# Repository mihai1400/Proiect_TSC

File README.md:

# Arhitectura Sistemului

## 1. Arhitectura Generală
Sistemul este construit în jurul **ESP32-C6-WROOM-1-N8** (microcontroler Wi-Fi 6 + Bluetooth 5 cu RISC-V) și include:

- **Alimentare & Baterie** (LDO, încărcător Li-Po, monitorizare nivel baterie)
- **Memorie** (Flash extern NOR 64MB, slot SD)
- **Senzori** (BME688 - temperatură/umiditate/presiune/VOC)
- **Afișaj** (E-Paper SPI)
- **Periferice** (RTC DS3231, butoane, LED-uri, USB-C)

## 2. Module & Interfețe cu ESP32-C6

### 2.1. Alimentare & Baterie
| Componentă                     | Interfață cu ESP32-C6       | Detalii                                  |
|--------------------------------|-----------------------------|------------------------------------------|
| LDO (XC6220A331MR-G)           | Nu (alimentare 3.3V)        | Reglează 3.3V pentru întreg sistemul     |
| Încărcător Baterie (MCP73831)  | GPIO4 (STAT)                | Semnalizează starea încărcării (LED)     |
| Monitor Baterie (MAX17048)     | I2C (SDA: GPIO8, SCL: GPIO9)| Măsoară nivelul bateriei (%/tensiune)    |

**Calcul consum:**
- ESP32-C6 (~80 mA în mod activ, ~5 µA în sleep)
- BME688 (~2.5 mA când active)
- E-Paper (~100 mA la refresh)
- **Total estimat:** ~200 mA (utilizare normală), sub 1 mA în sleep cu RTC activ

### 2.2. Memorie & Stocare
| Componentă            | Interfață cu ESP32-C6                          | Detalii                          |
|-----------------------|-----------------------------------------------|----------------------------------|
| Flash NOR (W25Q512JVEIQ) | SPI0 (CS: GPIO12, CLK: GPIO14, MOSI: GPIO13, MISO: GPIO11) | Stochează firmware/date |
| Slot SD (J4)          | SPI1 (CS: GPIO5, CLK: GPIO6, MOSI: GPIO7, MISO: GPIO10) | Stocare fișiere (FAT32) |

### 2.3. Senzori
| Componentă   | Interfață cu ESP32-C6       | Detalii                                  |
|--------------|-----------------------------|------------------------------------------|
| BME688       | I2C (SDA: GPIO8, SCL: GPIO9)| Senzor ambiental (temperatură, umiditate, presiune, VOC) |
| RTC (DS3231SN) | I2C (SDA: GPIO8, SCL: GPIO9)| Ceas precis (±2 ppm) cu alarmă           |

**Comunicație:**
- BME688 folosește I2C la 400 kHz (adresă `0x76`)
- DS3231 folosește I2C la 100 kHz (adresă `0x68`)

### 2.4. Afișaj E-Paper
| Componentă      | Interfață cu ESP32-C6                          | Detalii                          |
|-----------------|-----------------------------------------------|----------------------------------|
| Driver E-Paper  | SPI2 (CS: GPIO15, DC: GPIO16, RST: GPIO17, BUSY: GPIO18) | SPI dedicat pentru afișaj |

**Specificații:**
- Rezoluție: 800x600 (4.2" monocrom)
- Consum: ~100 mA la refresh, 0 mA în stare statică

### 2.5. Periferice & I/O
| Componentă   | Interfață cu ESP32-C6       | Detalii                                  |
|--------------|-----------------------------|------------------------------------------|
| Buton BOOT   | GPIO0                       | Resetare în mod flash                   |
| Buton CHANGE | GPIO1                       | Schimbă afișajul                        |
| LED-uri (D1-D12) | GPIO2, GPIO3            | Indicatori vizuali                      |
| USB-C (J1)   | GPIO20 (D+), GPIO21 (D-)    | Comunicație serială (CDC)               |

## 3. Alocarea Pinilor ESP32-C6
| Pin ESP32-C6 | Funcție       | Componentă            |
|--------------|---------------|-----------------------|
| GPIO0        | BOOT          | Buton BOOT            |
| GPIO1        | INPUT         | Buton CHANGE          |
| GPIO2-3      | OUTPUT        | LED-uri               |
| GPIO4        | INPUT         | MCP73831 (STAT)       |
| GPIO5        | CS            | Slot SD               |
| GPIO6-7      | SCK/MOSI      | Slot SD               |
| GPIO8-9      | SDA/SCL       | BME688 + DS3231 (I2C) |
| GPIO10       | MISO          | Slot SD               |
| GPIO11       | MISO          | Flash NOR             |
| GPIO12       | CS            | Flash NOR             |
| GPIO13-14    | MOSI/SCK      | Flash NOR             |
| GPIO15-18    | SPI EPD       | Afișaj E-Paper        |
| GPIO20-21    | USB D+/D-     | USB-C                 |

## 4. Optimizare Consum Energie
- **Sleep Mode:** ESP32-C6 intră în Deep Sleep cu RTC activ (~5 µA), trezit de DS3231 (alarmă) sau butoane
- **E-Paper:** Folosește energie doar la refresh
- **Senzori:** BME688 este pornit periodic (e.g., la 1 minut)

## 5. Diagramă

## 6. BOM

| Device Module                       | Amount | Datasheet | Shop |
| ----------------------------------- | ------ | -------| --------|
| 112A-TAAR-R03_ATTEND                | 1      | https://www.attend.com.tw/en/product.php?act=view&id=253 | https://www.digikey.com/en/products/detail/attend-technology/112A-TAAR-R03/17633923 |
| BD5229G-TR                          | 1      | https://www.digikey.ph/en/products/detail/rohm-semiconductor/BD5229G-TR/658502 | https://www.digikey.ph/en/products/detail/rohm-semiconductor/BD5229G-TR/658502 |
| BUTTON_COSYOMV1                     | 3      | https://components101.com/switches/push-button | https://uk.farnell.com/wurth-elektronik/430182043816/switch-160gf-6x6mm-smd-4-3mm-act/dp/2065105?CMP=GRHB-OEMSECRETS101 |
| CPH3225A                            | 1      | https://www.digikey.com/en/products/detail/seiko-instruments/CPH3225A/8692444 | https://www.digikey.com/en/products/detail/seiko-instruments/CPH3225A/8692444 |
| DS3231SN                            | 1      | https://www.digikey.com/en/products/detail/analog-devices-inc-maxim-integrated/DS3231SN/1197576 | https://www.digikey.com/en/products/detail/analog-devices-inc-maxim-integrated/DS3231SN/1197576 |
| BME680                              | 1      | https://www.sparkfun.com/sparkfun-environmental-sensor-breakout-bme680-qwiic.html | https://www.sparkfun.com/sparkfun-environmental-sensor-breakout-bme680-qwiic.html |
| MCP73831                            | 1      | https://www.microchip.com/en-us/product/mcp73831 | https://www.microchipdirect.com/product/MCP73831T-2ADI/OT |
| C6-WROOM-1-N8                       | 1      | https://www.espressif.com/sites/default/files/documentation/esp32-c6-wroom-1_wroom-1u_datasheet_en.pdf | https://www.adafruit.com/product/5671 |
| FH34SRJ-24S-0.5SH_99_               | 1      | https://www.hirose.com/product/p/CL0580-1255-6-99 | https://www.hirose.com/product/p/CL0580-1255-6-99 |
| MAX17048G+T10                       | 1      | https://eu.mouser.com/ProductDetail/Analog-Devices-Maxim-Integrated/MAX17048G+T10?qs=D7PJwyCwLAoGnnn8jEPRBQ%3D%3D | https://eu.mouser.com/ProductDetail/Analog-Devices-Maxim-Integrated/MAX17048G+T10?qs=D7PJwyCwLAoGnnn8jEPRBQ%3D%3D |
| MBR0530                             | 3      | https://www.digikey.com/en/products/detail/onsemi/MBR0530/1048783 | https://www.digikey.com/en/products/detail/onsemi/MBR0530/1048783 |
| PGB1010603MR                        | 6      | https://www.digikey.com/en/products/detail/littelfuse-inc/PGB1010603MR/715755 | https://www.digikey.com/en/products/detail/littelfuse-inc/PGB1010603MR/715755 |
| SAMACSYS_PARTS_USB4110-GF-A         | 1      | https://www.digikey.ro/en/products/detail/gct/USB4110-GF-A/10384547 | https://www.digikey.ro/en/products/detail/gct/USB4110-GF-A/10384547 |
| SI1308EDL-T1-GE3                    | 1      | https://www.digikey.com/en/products/detail/vishay-siliconix/SI1308EDL-T1-GE3/4876435 | https://www.digikey.com/en/products/detail/vishay-siliconix/SI1308EDL-T1-GE3/4876435 |
| SJ                                  | 1      | https://www.digikey.com/en/products/detail/cui-devices/SJ1-3514N/738685 | https://www.digikey.com/en/products/detail/cui-devices/SJ1-3514N/738685 |
| USBLC6-2SC6Y                        | 1      | https://www.digikey.com/en/products/detail/stmicroelectronics/USBLC6-2SC6Y/2819177 | https://www.digikey.com/en/products/detail/stmicroelectronics/USBLC6-2SC6Y/2819177 |
| W25Q512JVEIQ                        | 1      | https://www.digikey.com/en/products/detail/winbond-electronics/W25Q512JVEIQ/10244706 | https://www.digikey.com/en/products/detail/winbond-electronics/W25Q512JVEIQ/10244706 |
| XC6220A331MR-G                      | 1      | https://www.digikey.com/en/products/detail/torex-semiconductor-ltd/XC6220B331MR-G/2138177 | https://www.digikey.com/en/products/detail/torex-semiconductor-ltd/XC6220B331MR-G/2138177 |
| SD0805S020S1R0                      | 2      | https://www.digikey.com/en/products/detail/kyocera-avx/SD0805S020S1R0/3749517 | https://www.digikey.com/en/products/detail/kyocera-avx/SD0805S020S1R0/3749517 |
| LTSPICE_C 100nF                     | 8      | https://www.digikey.com/en/products/detail/nextgen-components/0402B104K500HI/22601924 | https://www.digikey.com/en/products/detail/nextgen-components/0402B104K500HI/22601924 |
| LTSPICE_C 10nF                      | 1      | https://www.amazon.com/ALLECIN-Electrolytic-Capacitor-0-2x0-43in-Capacitors/dp/B0CMQC587X/ref=sr_1_1_sspa?sr=8-1-spons&sp_csd=d2lkZ2V0TmFtZT1zcF9hdGY&psc=1 | https://www.amazon.com/ALLECIN-Electrolytic-Capacitor-0-2x0-43in-Capacitors/dp/B0CMQC587X/ref=sr_1_1_sspa?sr=8-1-spons&sp_csd=d2lkZ2V0TmFtZT1zcF9hdGY&psc=1 |
| LTSPICE_C 4.7uF                     | 6      | https://www.amazon.com/ALLECIN-Electrolytic-Capacitor-0-2x0-43in-Capacitors/dp/B0CMQC587X/ref=sr_1_1_sspa?sr=8-1-spons&sp_csd=d2lkZ2V0TmFtZT1zcF9hdGY&psc=1 | https://www.amazon.com/ALLECIN-Electrolytic-Capacitor-0-2x0-43in-Capacitors/dp/B0CMQC587X/ref=sr_1_1_sspa?sr=8-1-spons&sp_csd=d2lkZ2V0TmFtZT1zcF9hdGY&psc=1 |
| LTSPICE_C 1uF                       | 10     | https://www.amazon.com/ALLECIN-Electrolytic-Capacitor-0-2x0-43in-Capacitors/dp/B0CMQC587X/ref=sr_1_1_sspa?sr=8-1-spons&sp_csd=d2lkZ2V0TmFtZT1zcF9hdGY&psc=1 | https://www.amazon.com/ALLECIN-Electrolytic-Capacitor-0-2x0-43in-Capacitors/dp/B0CMQC587X/ref=sr_1_1_sspa?sr=8-1-spons&sp_csd=d2lkZ2V0TmFtZT1zcF9hdGY&psc=1 |
| LTSPICE_C 0.1uF                     | 1      | https://www.digikey.com/en/products/detail/samsung-electro-mechanics/CL10E104KC8VPNC/20498486 | https://www.digikey.com/en/products/detail/samsung-electro-mechanics/CL10E104KC8VPNC/20498486 |
| ADAFRUIT_LED                        | 1      | https://www.adafruit.com/product/4684 | https://www.adafruit.com/product/4684 |
| ESP32_VARISTOR                      | 1      | https://uk.rs-online.com/web/p/varistors/9012743 | https://uk.rs-online.com/web/p/varistors/9012743 |
| CT3528 (RCL_CPOL-EU) 100uF          | 1      | https://www.datasheetarchive.com/?q=ct3528 |  |
| DMG2305UX-7 20V/4.2A/52mO/1.4W      | 2      | https://www.digikey.com/en/products/detail/diodes-incorporated/DMG2305UX-7/4340667 | https://www.digikey.com/en/products/detail/diodes-incorporated/DMG2305UX-7/4340667 |
| IND-4828-WE-TPC-WRE                 | 1      | https://www.axel-gl.com/en/asone/d/64-0172-48/ | https://www.axel-gl.com/en/asone/d/64-0172-48/ |
| JS-1MM(QWIIC_CONNECTOR)             | 1      | https://www.sparkfun.com/qwiic-jst-connector-smd-4-pin-horizontal.html | https://www.sparkfun.com/qwiic-jst-connector-smd-4-pin-horizontal.html |
| LTSPICE_R 5k1                       | 2      |  | https://www.amazon.com/BOJACK-Values-Resistor-Resistors-Assortment/dp/B08FD1XVL6/ref=sr_1_1_sspa?sr=8-1-spons&sp_csd=d2lkZ2V0TmFtZT1zcF9hdGY |
| LTSPICE_R 100k                      | 1      |  | https://www.amazon.com/BOJACK-Values-Resistor-Resistors-Assortment/dp/B08FD1XVL6/ref=sr_1_1_sspa?sr=8-1-spons&sp_csd=d2lkZ2V0TmFtZT1zcF9hdGY |
| LTSPICE_R 2.2                       | 1      |  | https://www.amazon.com/BOJACK-Values-Resistor-Resistors-Assortment/dp/B08FD1XVL6/ref=sr_1_1_sspa?sr=8-1-spons&sp_csd=d2lkZ2V0TmFtZT1zcF9hdGY |
| LTSPICE_R 10k                       | 16     |  | https://www.amazon.com/BOJACK-Values-Resistor-Resistors-Assortment/dp/B08FD1XVL6/ref=sr_1_1_sspa?sr=8-1-spons&sp_csd=d2lkZ2V0TmFtZT1zcF9hdGY |
| LTSPICE_R 0.47                      | 1      |  | https://www.amazon.com/BOJACK-Values-Resistor-Resistors-Assortment/dp/B08FD1XVL6/ref=sr_1_1_sspa?sr=8-1-spons&sp_csd=d2lkZ2V0TmFtZT1zcF9hdGY |
| LTSPICE_R 2k                        | 1      |  | https://www.amazon.com/BOJACK-Values-Resistor-Resistors-Assortment/dp/B08FD1XVL6/ref=sr_1_1_sspa?sr=8-1-spons&sp_csd=d2lkZ2V0TmFtZT1zcF9hdGY |
| LTSPICE_R 200                       | 1      |  | https://www.amazon.com/BOJACK-Values-Resistor-Resistors-Assortment/dp/B08FD1XVL6/ref=sr_1_1_sspa?sr=8-1-spons&sp_csd=d2lkZ2V0TmFtZT1zcF9hdGY |
| LTSPICE_R 15                        | 1      |  | https://www.amazon.com/BOJACK-Values-Resistor-Resistors-Assortment/dp/B08FD1XVL6/ref=sr_1_1_sspa?sr=8-1-spons&sp_csd=d2lkZ2V0TmFtZT1zcF9hdGY |
| Test Pad TP20R                      | 17     | https://us.misumi-ec.com/vona2/detail/221005496391/?HissuCode=TP20R-24 | https://us.misumi-ec.com/vona2/detail/221005496391/?HissuCode=TP20R-24 |

## 7. Concluzii
- ESP32-C6 este nucleul sistemului, cu 3 interfețe SPI (Flash, SD, E-Paper) și I2C partajat (BME688 + DS3231)
- BME688 oferă date ambientale, iar DS3231 menține timpul precis
- Consum redus în sleep (~5 µA) permite funcționare pe baterie >1 lună

Probleme : 
 - Nu pot genera fiserul .step (se blocheaza Fusion-ul cand incerc)

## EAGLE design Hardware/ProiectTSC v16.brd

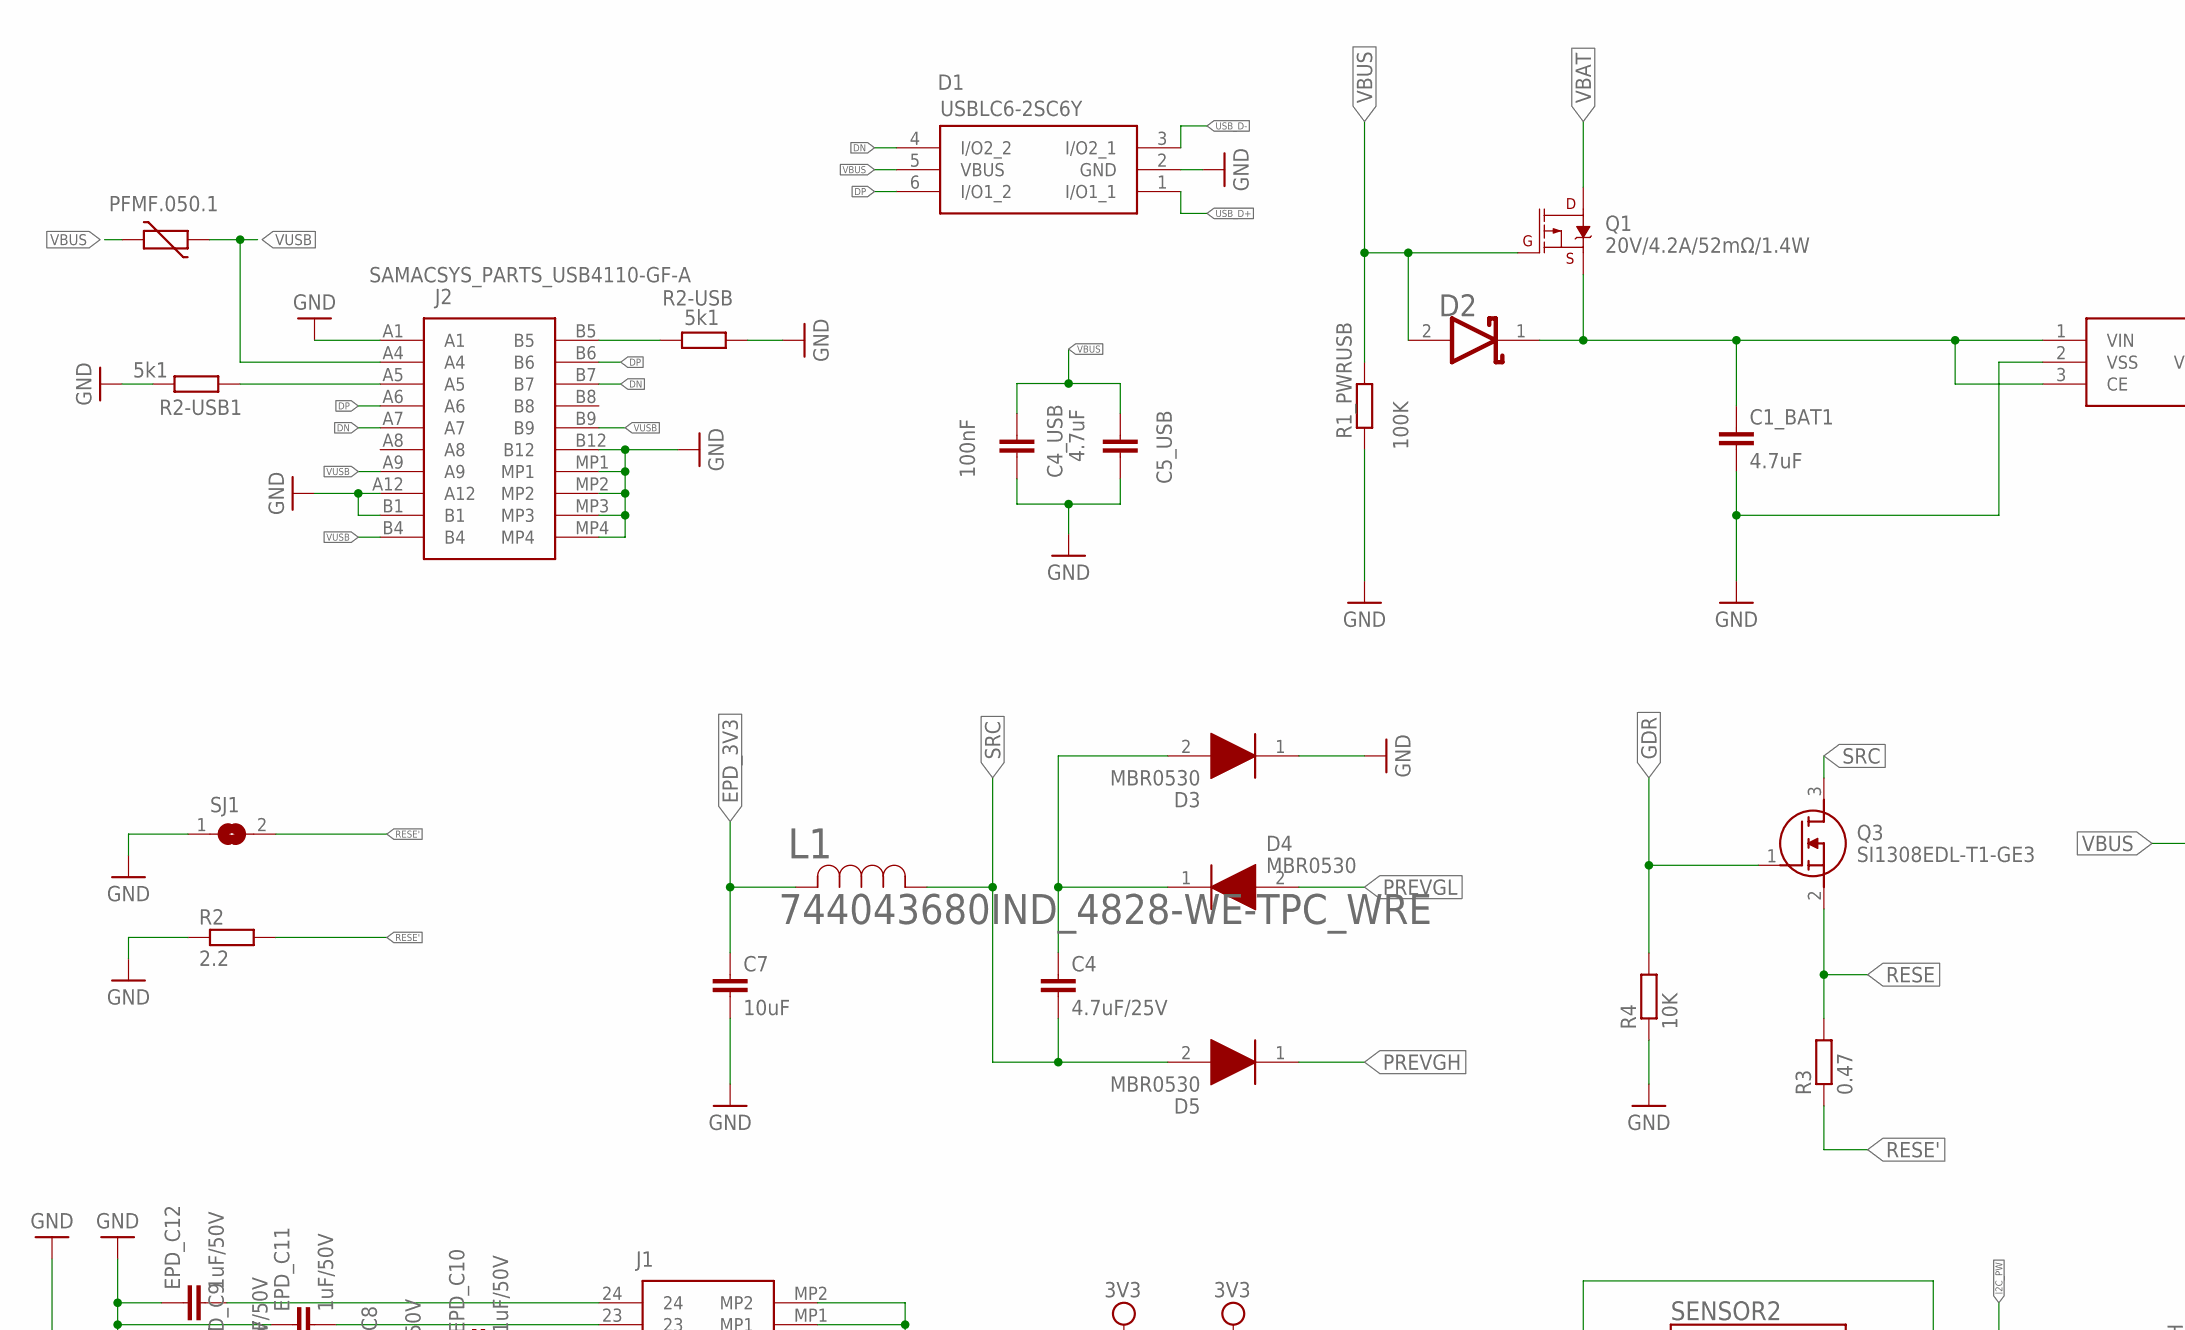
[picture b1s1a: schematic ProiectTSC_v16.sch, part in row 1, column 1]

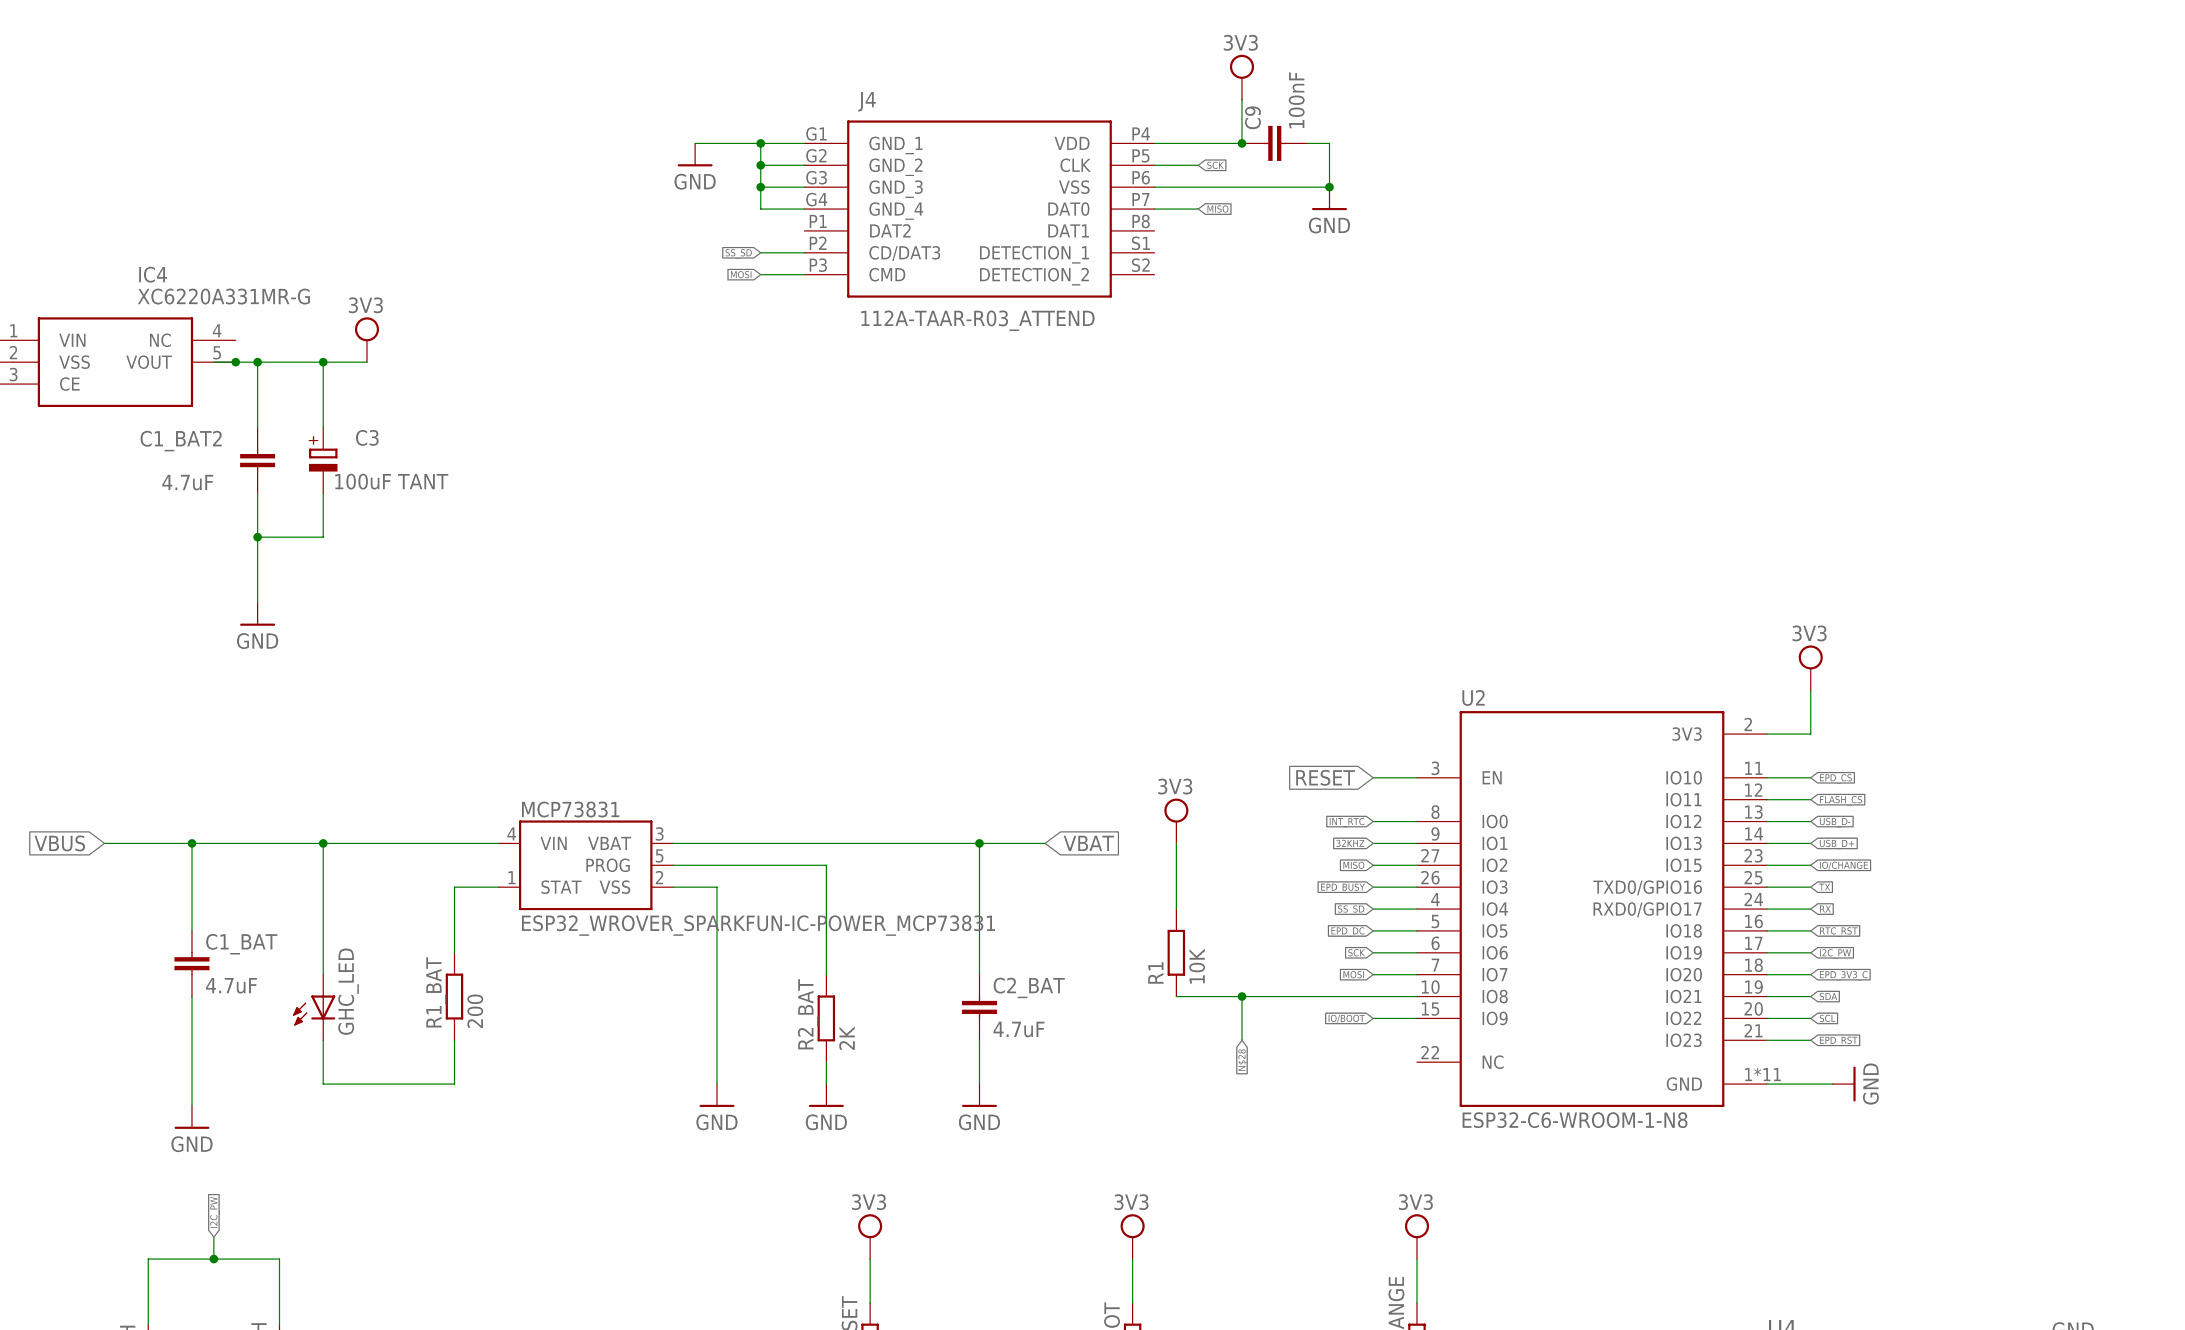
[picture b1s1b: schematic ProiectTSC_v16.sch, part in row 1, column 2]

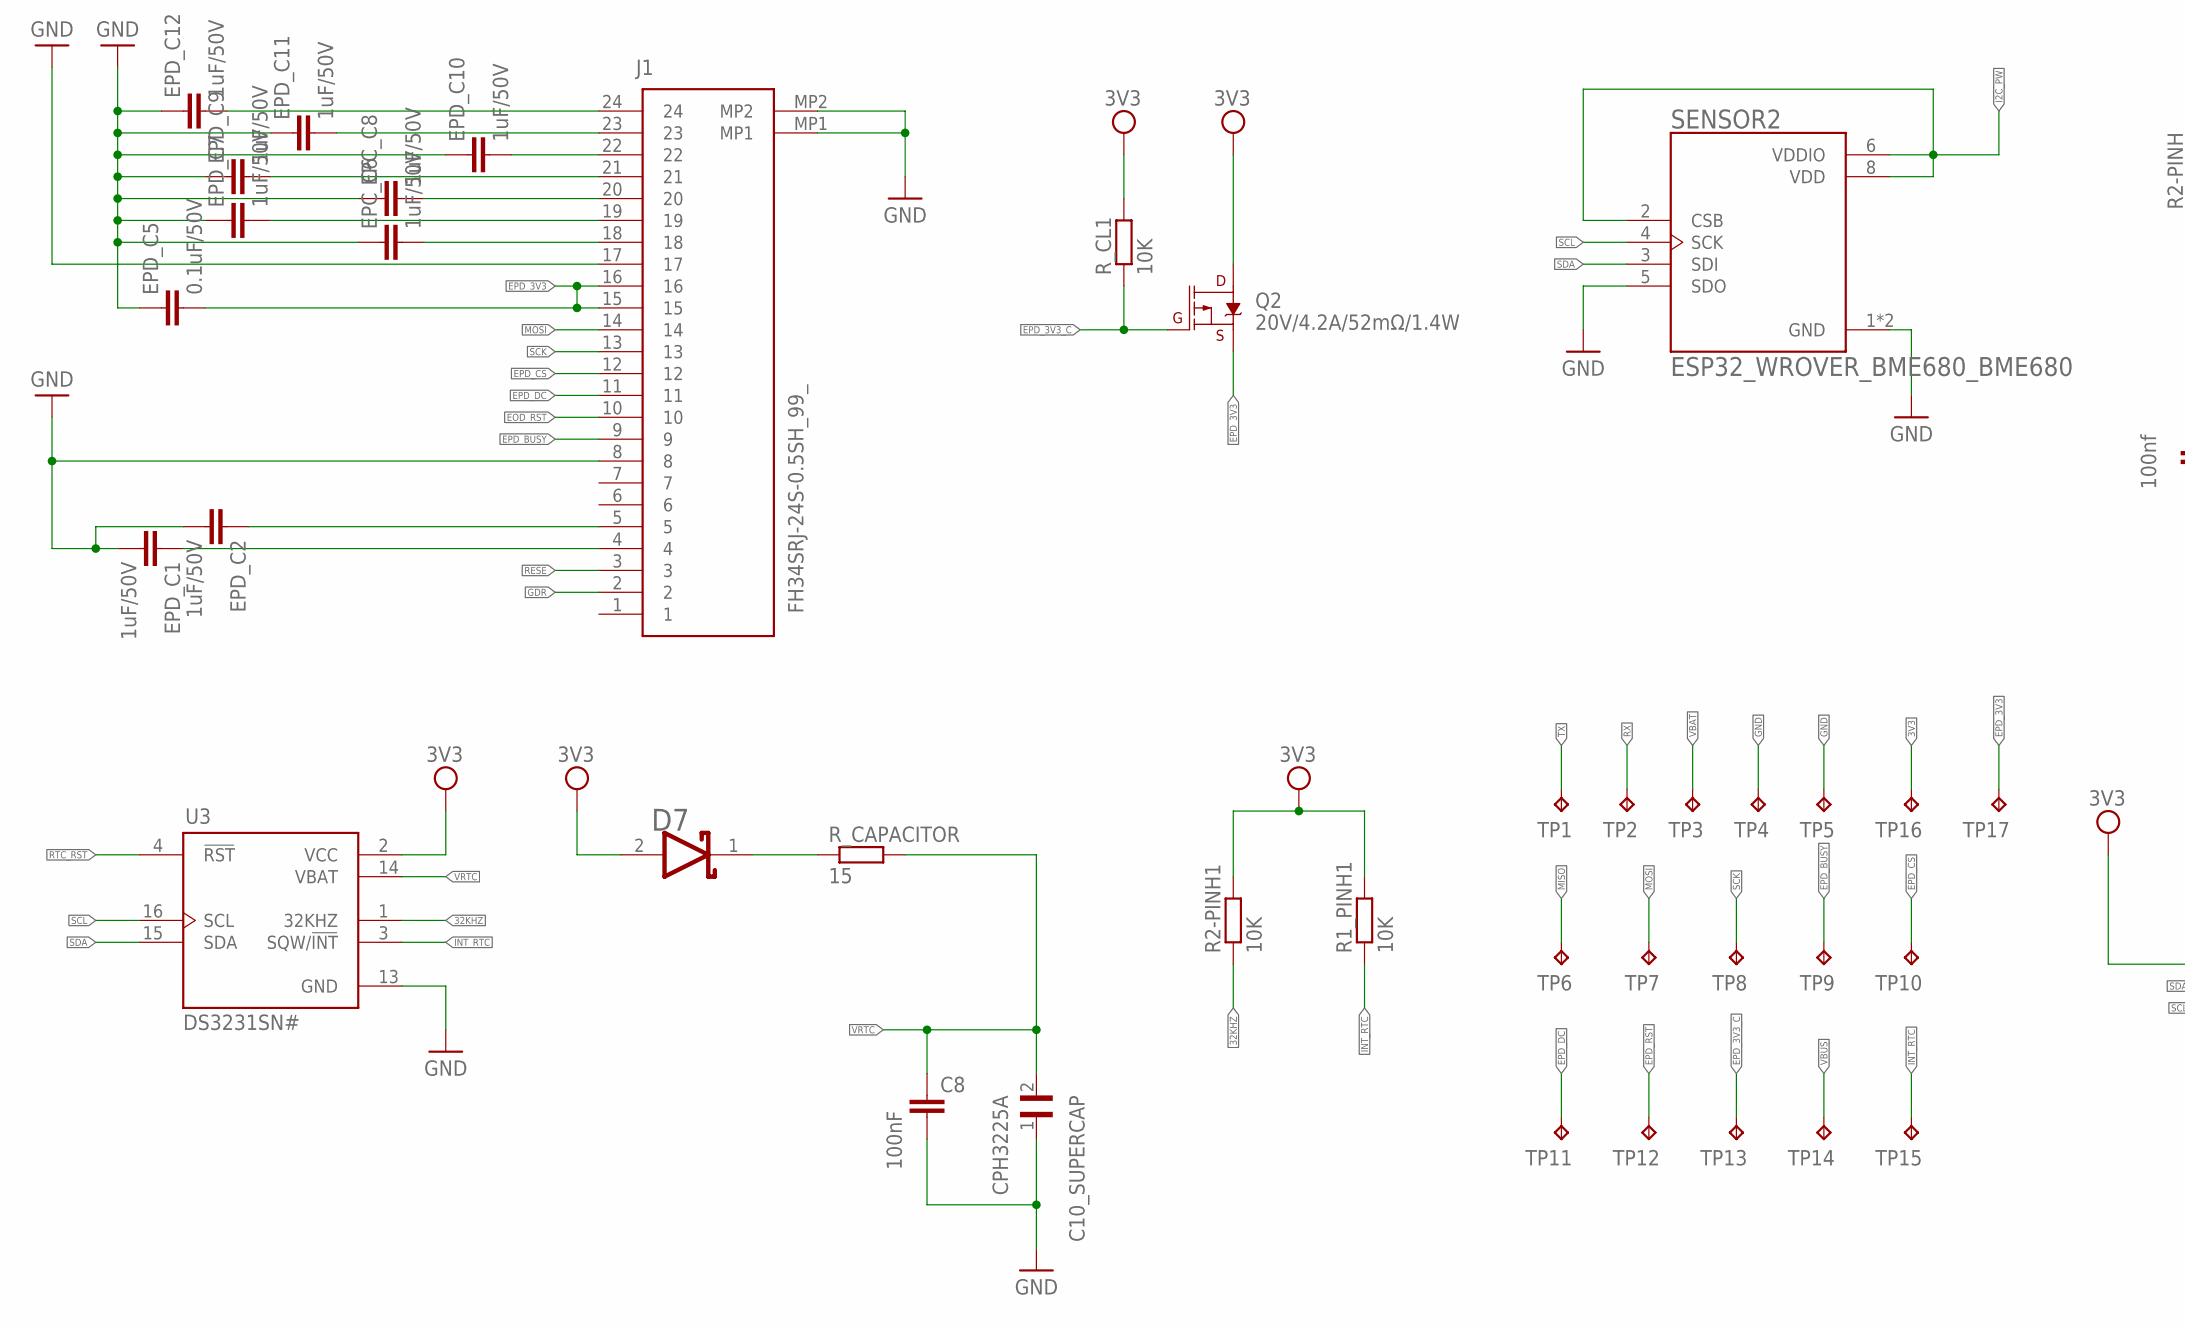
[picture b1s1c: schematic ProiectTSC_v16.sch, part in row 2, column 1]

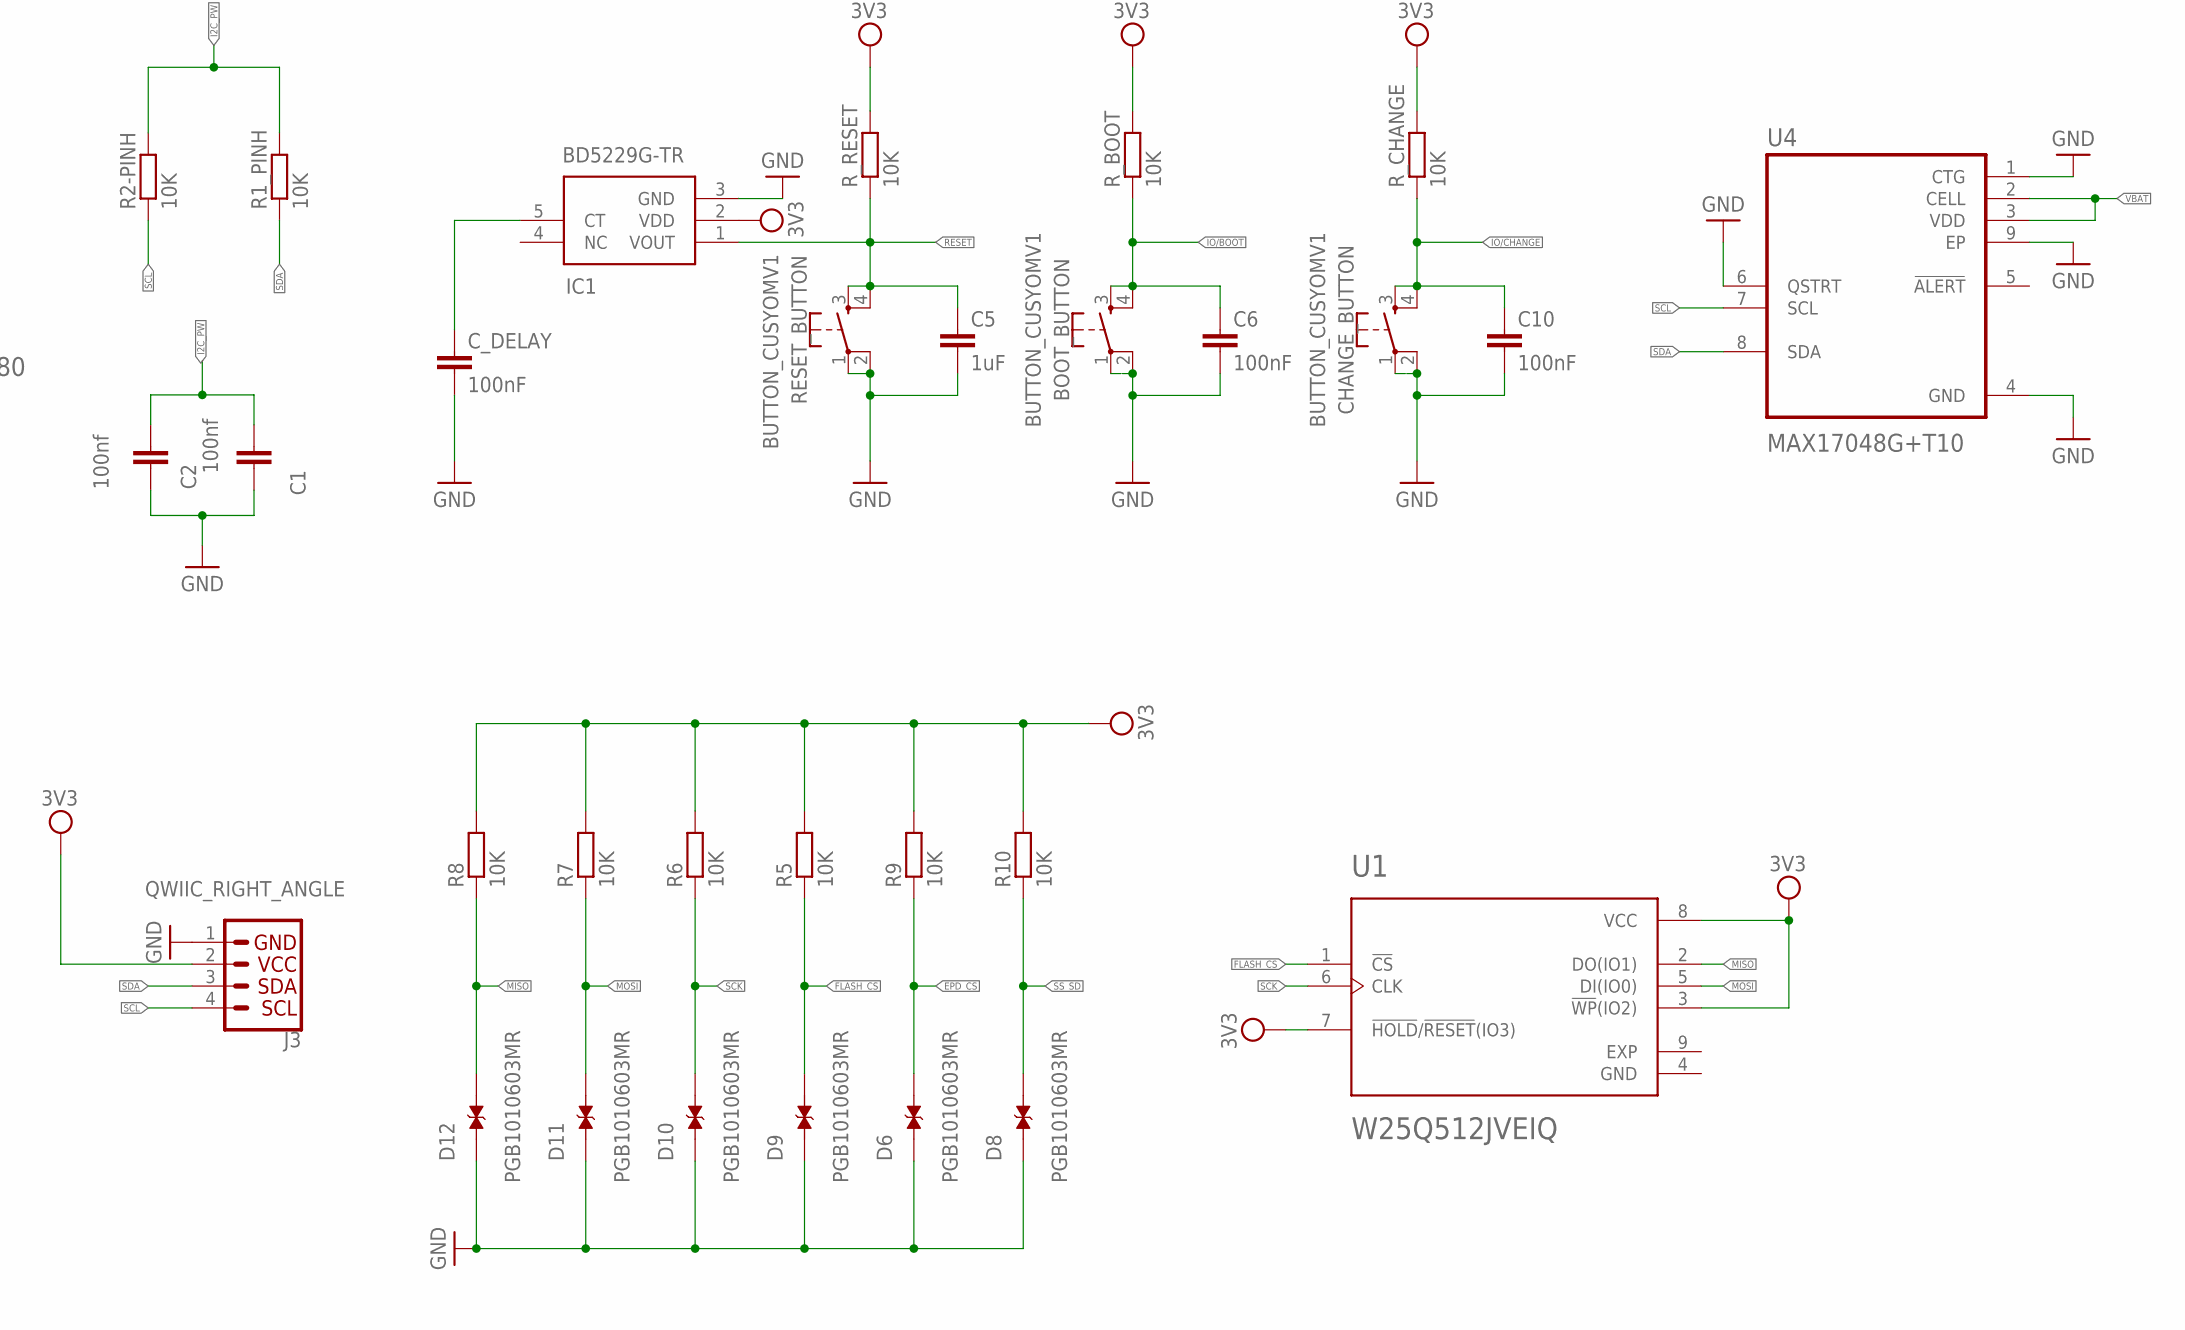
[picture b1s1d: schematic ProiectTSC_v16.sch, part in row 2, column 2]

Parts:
BOOT_BUTTON: BUTTON_CUSYOMV1; MYBUTTON
C1, C2: 100nf; ESP32_WROVER_EAGLE-LTSPICE_C0402
C1_BAT, C1_BAT1, C1_BAT2, C2_BAT, C5_USB: 4.7uF; ESP32_WROVER_EAGLE-LTSPICE_C0402
C3: 100uF TANT; RCL_CT3528
C4: 4.7uF/25V; ESP32_WROVER_EAGLE-LTSPICE_C0402
C4_USB, C6, C8, C9, C10: 100nF; ESP32_WROVER_EAGLE-LTSPICE_C0402
C5: 1uF; ESP32_WROVER_EAGLE-LTSPICE_C0402
C7: 10uF; ESP32_WROVER_EAGLE-LTSPICE_C0402
C10_SUPERCAP: CPH3225A; CAPCP3225X100N
CHANGE_BUTTON: BUTTON_CUSYOMV1; MYBUTTON
C_DELAY: 100nF; ESP32_WROVER_EAGLE-LTSPICE_C0402
D1: USBLC6-2SC6Y; SOT95P280X145-6N
D2, D7: ESP32_WROVER_AVX---SD0805S020S1R0_AVX_SD0805S020S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; ESP32_WROVER_AVX---SD0805S020S1R0_AVX_SD0805S020S1R0_0
D3, D4, D5: MBR0530; SOD3716X135N
D6, D8, D9, D10, D11, D12: PGB1010603MR; DIOC1608X36N
EPC_C6, EPC_C8: 1uF/50V; ESP32_WROVER_EAGLE-LTSPICE_C0402
EPD_C1, EPD_C2, EPD_C7, EPD_C9, EPD_C10, EPD_C11, EPD_C12: 1uF/50V; ESP32_WROVER_EAGLE-LTSPICE_C0402
EPD_C5: 0.1uF/50V; ESP32_WROVER_EAGLE-LTSPICE_C0402
GHC_LED: ADAFRUIT_LEDCHIP-LED0603; ADAFRUIT_CHIP-LED0603
IC1: BD5229G-TR; SOT95P280X125-5N
IC4: XC6220A331MR-G; SOT95P280X120-5N
J1: FH34SRJ-24S-0.5SH_99_; FH34SRJ24S05SH99
J2: SAMACSYS_PARTS_USB4110-GF-A; SAMACSYS_PARTS_USB4110GFA
J3: QWIIC_RIGHT_ANGLE; JST04_1MM_RA
J4: 112A-TAAR-R03_ATTEND; 112ATAARR03ATTEND
L1: 744043680IND_4828-WE-TPC_WRE; IND_4828-WE-TPC_WRE
MCP73831: ESP32_WROVER_SPARKFUN-IC-POWER_MCP73831; ESP32_WROVER_SPARKFUN-IC-POWER_SOT23-5
PFMF.050.1: ESP32C6_VARISTORCN1812; ESP32C6_VARISTOR_CT/CN1812
Q1, Q2: 20V/4.2A/52mΩ/1.4W; ESP32_WROVER_SPARKFUN-DISCRETESEMI_SOT23-3
Q3: SI1308EDL-T1-GE3; SOT65P210X110-3N
R1, R1_PINH, R1_PINH1, R2-PINH, R2-PINH1, R4, R5, R6, R7, R8, R9, R10: 10K; ESP32_WROVER_EAGLE-LTSPICE_R0402
R1_BAT: 200; ESP32_WROVER_EAGLE-LTSPICE_R0402
R1_PWRUSB: ESP32_WROVER_EAGLE-LTSPICE_RR0402; ESP32_WROVER_EAGLE-LTSPICE_R0402
R2: 2.2; ESP32_WROVER_EAGLE-LTSPICE_R0402
R2-USB, R2-USB1: 5k1; ESP32_WROVER_EAGLE-LTSPICE_R0402
R2_BAT: 2K; ESP32_WROVER_EAGLE-LTSPICE_R0402
R3: 0.47; ESP32_WROVER_EAGLE-LTSPICE_R0402
RESET_BUTTON: BUTTON_CUSYOMV1; MYBUTTON
R_BOOT: 10K; ESP32_WROVER_EAGLE-LTSPICE_R0402
R_CAPACITOR: 15; ESP32_WROVER_EAGLE-LTSPICE_R0402
R_CHANGE: 10K; ESP32_WROVER_EAGLE-LTSPICE_R0402
R_CL1: 10K; ESP32_WROVER_EAGLE-LTSPICE_R0402
R_RESET: 10K; ESP32_WROVER_EAGLE-LTSPICE_R0402
SENSOR2: ESP32_WROVER_BME680_BME680; ESP32_WROVER_BME680_PSON80P300X300X100-8N
SJ1: SJ
TP1, TP2, TP3, TP4, TP5, TP6, TP7, TP8, TP9, TP10, TP11, TP12, TP13, TP14, TP15, TP16, TP17: TPTP20R; TP20R
U1: W25Q512JVEIQ; SON127P600X800X80-9N
U2: ESP32-C6-WROOM-1-N8; XCVR_ESP32-C6-WROOM-1-N8
U3: DS3231SN#; SOIC127P1032X265-16N
U4: MAX17048G+T10; SON50P200X200X80-9N

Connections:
3V3: C1_BAT2.1, C3.+, C9.1, D7.2 (ANODE), IC1.2 (VDD), IC4.5 (VOUT), J3.2, J4.P4 (VDD), Q2.3 (D), R1.2, R1_PINH1.2, R2-PINH1.2, R5.2, R6.2, R7.2, R8.2, R9.2, R10.2, R_BOOT.2, R_CHANGE.2, R_CL1.2, R_RESET.2, TP16.TP, U1.3 (!WP!(IO2)), U1.7 (!HOLD!/!RESET!(IO3)), U1.8 (VCC), U2.2 (3V3), U3.2 (VCC)
32KHZ: R2-PINH1.1, U2.9 (IO1), U3.1 (32KHZ)
DP: J2.A6
EOD_RST: J1.10
EPD_3V3: C7.1, EPD_C5.2, J1.15, J1.16, L1.2, Q2.2 (S), TP17.TP
EPD_3V3_C: Q2.1 (G), R_CL1.1, TP13.TP, U2.18 (IO20)
EPD_BUSY: J1.9, TP9.TP, U2.26 (IO3)
EPD_CS: D6.2, J1.12, R9.1, TP10.TP, U2.11 (IO10)
EPD_DC: J1.11, TP11.TP, U2.5 (IO5)
EPD_RST: TP12.TP, U2.21 (IO23)
FLASH_CS: D9.2, R5.1, U1.1 (!CS), U2.12 (IO11)
GDR: J1.2, Q3.1 (G), R4.2
GND: BOOT_BUTTON.2, C1.2, C1_BAT.2, C1_BAT1.2, C1_BAT2.2, C2.2, C2_BAT.2, C3.-, C4_USB.2, C5.2, C5_USB.2, C6.2, C7.2, C8.2, C9.2, C10.2, C10_SUPERCAP.1, CHANGE_BUTTON.2, C_DELAY.2, D1.2 (GND), D3.1 (K), D6.1, D8.1, D9.1, D10.1, D11.1, D12.1, EPC_C6.1, EPC_C8.1, EPD_C1.2, EPD_C2.2, EPD_C5.1, EPD_C7.1, EPD_C9.1, EPD_C10.1, EPD_C11.1, EPD_C12.1, IC1.3 (GND), IC4.2 (VSS), J1.8, J1.17, J1.MP1, J1.MP2, J2.A1, J2.A12, J2.B1, J2.B12, J2.MP1, J2.MP2, J2.MP3, J2.MP4, J3.1, J4.G1 (GND_1), J4.G2 (GND_2), J4.G3 (GND_3), J4.G4 (GND_4), J4.P6 (VSS), MCP73831.2 (VSS), R1_PWRUSB.1, R2.1, R2-USB.2, R2-USB1.1, R2_BAT.1, R4.1, RESET_BUTTON.1, RESET_BUTTON.2, SENSOR2.1 (GND), SENSOR2.5 (SDO), SENSOR2.7 (GND), SJ1.1, TP4.TP, TP5.TP, U1.4 (GND), U2.1 (GND), U2.28 (GND), U2.29_1 (GND), U2.29_2 (GND), U2.29_3 (GND), U2.29_4 (GND), U2.29_5 (GND), U2.29_6 (GND), U2.29_7 (GND), U2.29_8 (GND), U2.29_9 (GND), U3.13 (GND), U4.1 (CTG), U4.4 (GND), U4.6 (QSTRT), U4.9 (EP)
I2C_PW: C1.1, C2.1, R1_PINH.2, R2-PINH.2, SENSOR2.2 (CSB), SENSOR2.6 (VDDIO), SENSOR2.8 (VDD), U2.17 (IO19)
INT_RTC: R1_PINH1.1, TP15.TP, U2.8 (IO0), U3.3 (SQW/!INT)
IO/BOOT: BOOT_BUTTON.3, BOOT_BUTTON.4, C6.1, R_BOOT.1, U2.15 (IO9)
IO/CHANGE: C10.1, CHANGE_BUTTON.3, CHANGE_BUTTON.4, R_CHANGE.1, U2.23 (IO15)
MISO: D12.2, J4.P7 (DAT0), R8.1, TP6.TP, U1.2 (DO(IO1)), U2.27 (IO2)
MOSI: D11.2, J1.14, R7.1, TP7.TP, U1.5 (DI(IO0)), U2.7 (IO7)
unnamed: J2.A5, R2-USB1.2
unnamed: J2.B5, R2-USB.1
unnamed: C1_BAT1.1, D2.1 (CATHODE), IC4.1 (VIN), IC4.3 (CE), Q1.2 (S)
unnamed: C4.1, D3.2 (A), D4.1 (K)
unnamed: GHC_LED.C, R1_BAT.1
unnamed: MCP73831.1 (STAT), R1_BAT.2
unnamed: EPD_C12.2, J1.24
unnamed: MCP73831.5 (PROG), R2_BAT.2
unnamed: EPD_C11.2, J1.23
unnamed: EPD_C10.2, J1.22
unnamed: EPD_C9.2, J1.21
unnamed: EPC_C8.2, J1.20
unnamed: EPD_C7.2, J1.19
unnamed: EPC_C6.2, J1.18
unnamed: EPD_C2.1, J1.5
unnamed: EPD_C1.1, J1.4
unnamed: R1.1, U2.10 (IO8)
unnamed: D7.1 (CATHODE), R_CAPACITOR.1
unnamed: C_DELAY.1, IC1.5 (CT)
PREVGH: D5.1 (K)
PREVGL: D4.2 (A)
RESE: J1.3, Q3.2 (S), R3.2
RESE': R2.2, R3.1, SJ1.2
RESET: C5.1, IC1.1 (VOUT), RESET_BUTTON.3, RESET_BUTTON.4, R_RESET.1, U2.3 (EN)
RTC_RST: U2.16 (IO18), U3.4 (!RST)
RX: TP2.TP, U2.24 (RXD0/GPIO17)
SCK: D10.2, J1.13, J4.P5 (CLK), R6.1, TP8.TP, U1.6 (CLK), U2.6 (IO6)
SCL: J3.4, R2-PINH.1, SENSOR2.4 (SCK), U2.20 (IO22), U3.16 (SCL), U4.7 (SCL)
SDA: J3.3, R1_PINH.1, SENSOR2.3 (SDI), U2.19 (IO21), U3.15 (SDA), U4.8 (SDA)
SRC: C4.2, D5.2 (A), L1.1, Q3.3 (D)
SS_SD: D8.2, J4.P2 (CD/DAT3), R10.1, U2.4 (IO4)
TX: TP1.TP, U2.25 (TXD0/GPIO16)
USB_D+: U2.14 (IO13)
USB_D-: D1.3 (I/O2_1), U2.13 (IO12)
VBAT: C2_BAT.1, MCP73831.3 (VBAT), Q1.3 (D), TP3.TP, U4.2 (CELL), U4.3 (VDD)
VBUS: C1_BAT.1, C4_USB.1, C5_USB.1, D2.2 (ANODE), GHC_LED.A, MCP73831.4 (VIN), PFMF.050.1.2, Q1.1 (G), R1_PWRUSB.2, TP14.TP
VRTC: C8.1, C10_SUPERCAP.2, R_CAPACITOR.2, U3.14 (VBAT)
VUSB: J2.A4, PFMF.050.1.1

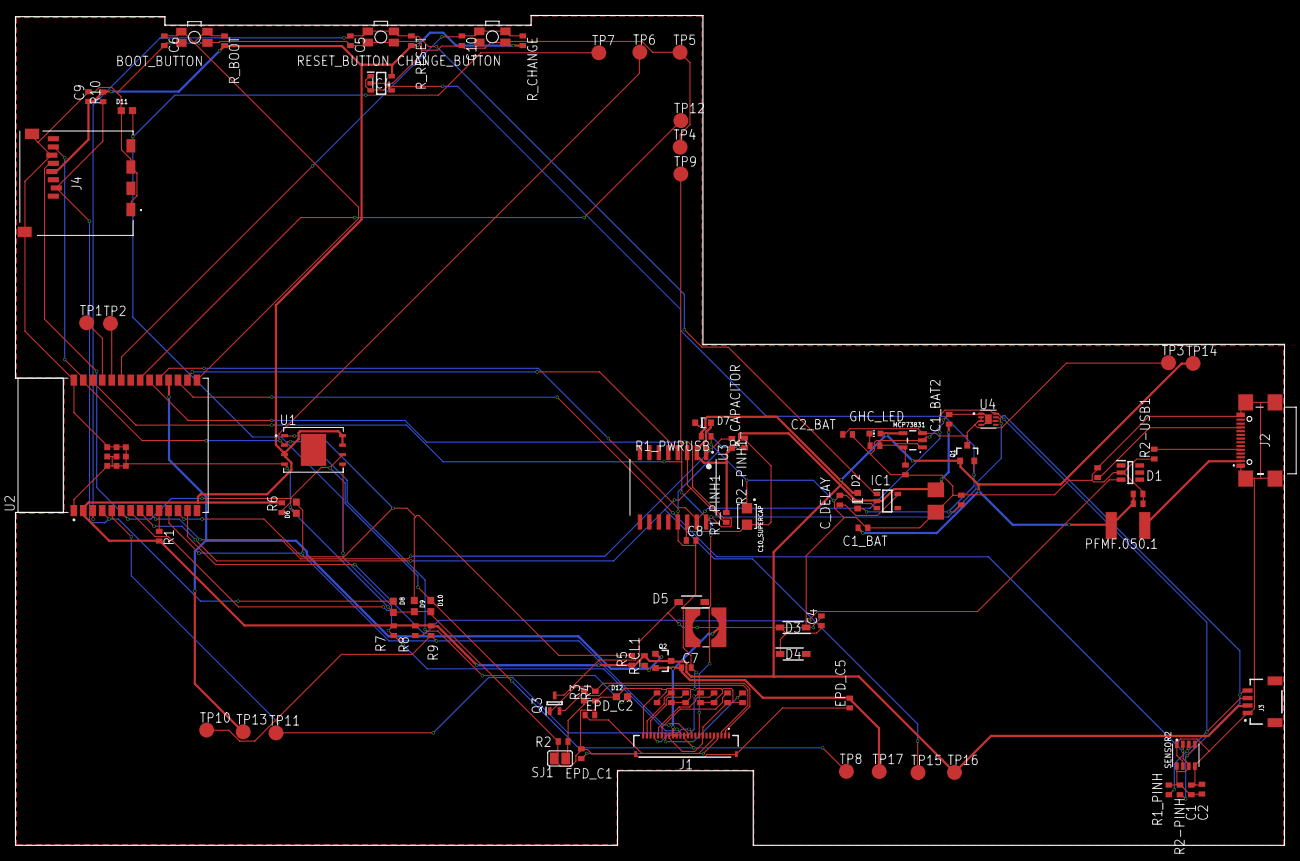
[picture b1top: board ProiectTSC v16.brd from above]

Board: 2 copper layers, 170.2 x 111.3 mm, 103 parts (0 on the bottom side), 52 nets.

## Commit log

2025-04-06 Create LICENSE

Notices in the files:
parts and their libraries:
COPYRIGHT: Copyright (C) 2024 Ultra Librarian. All rights reserved.
